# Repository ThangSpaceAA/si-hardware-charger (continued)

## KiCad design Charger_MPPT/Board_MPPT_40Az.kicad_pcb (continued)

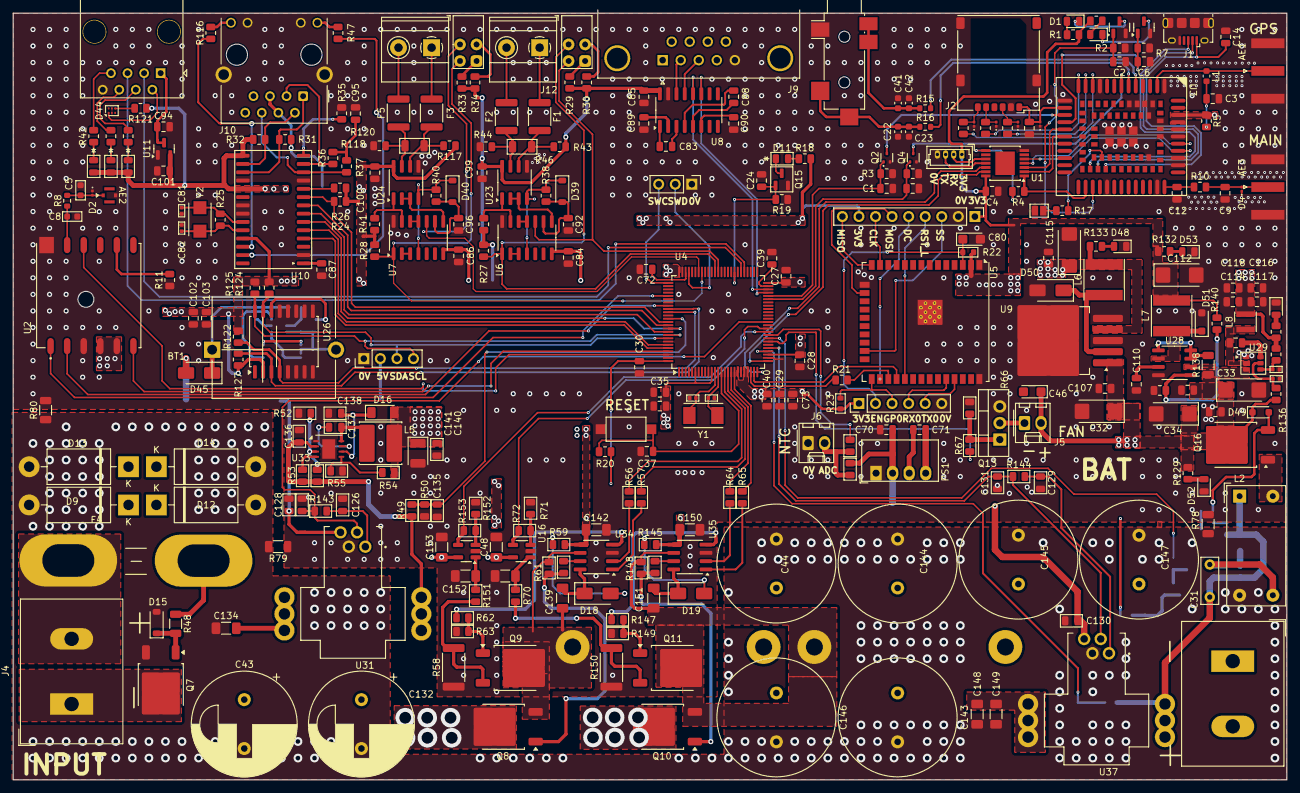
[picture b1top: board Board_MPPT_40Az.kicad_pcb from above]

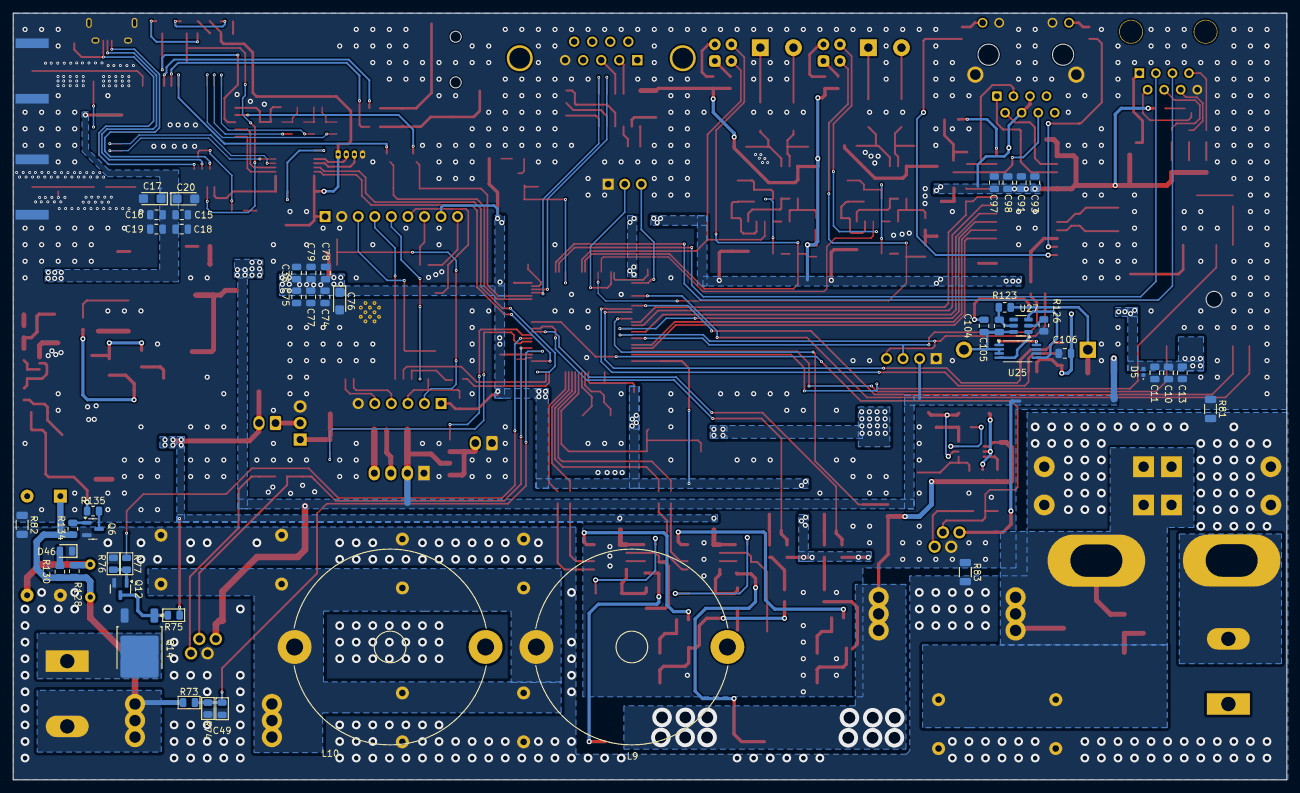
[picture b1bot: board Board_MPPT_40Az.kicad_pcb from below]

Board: 2 copper layers, 195.4 x 117.6 mm, 359 parts (47 on the bottom side), 235 nets.

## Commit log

2025-07-29 added file hardware charger mppt
2025-07-29 add submodule to repo
2025-07-30 added order link
2025-08-01 final link order
2025-08-02 added 3d model
2025-08-05 added 3d models
